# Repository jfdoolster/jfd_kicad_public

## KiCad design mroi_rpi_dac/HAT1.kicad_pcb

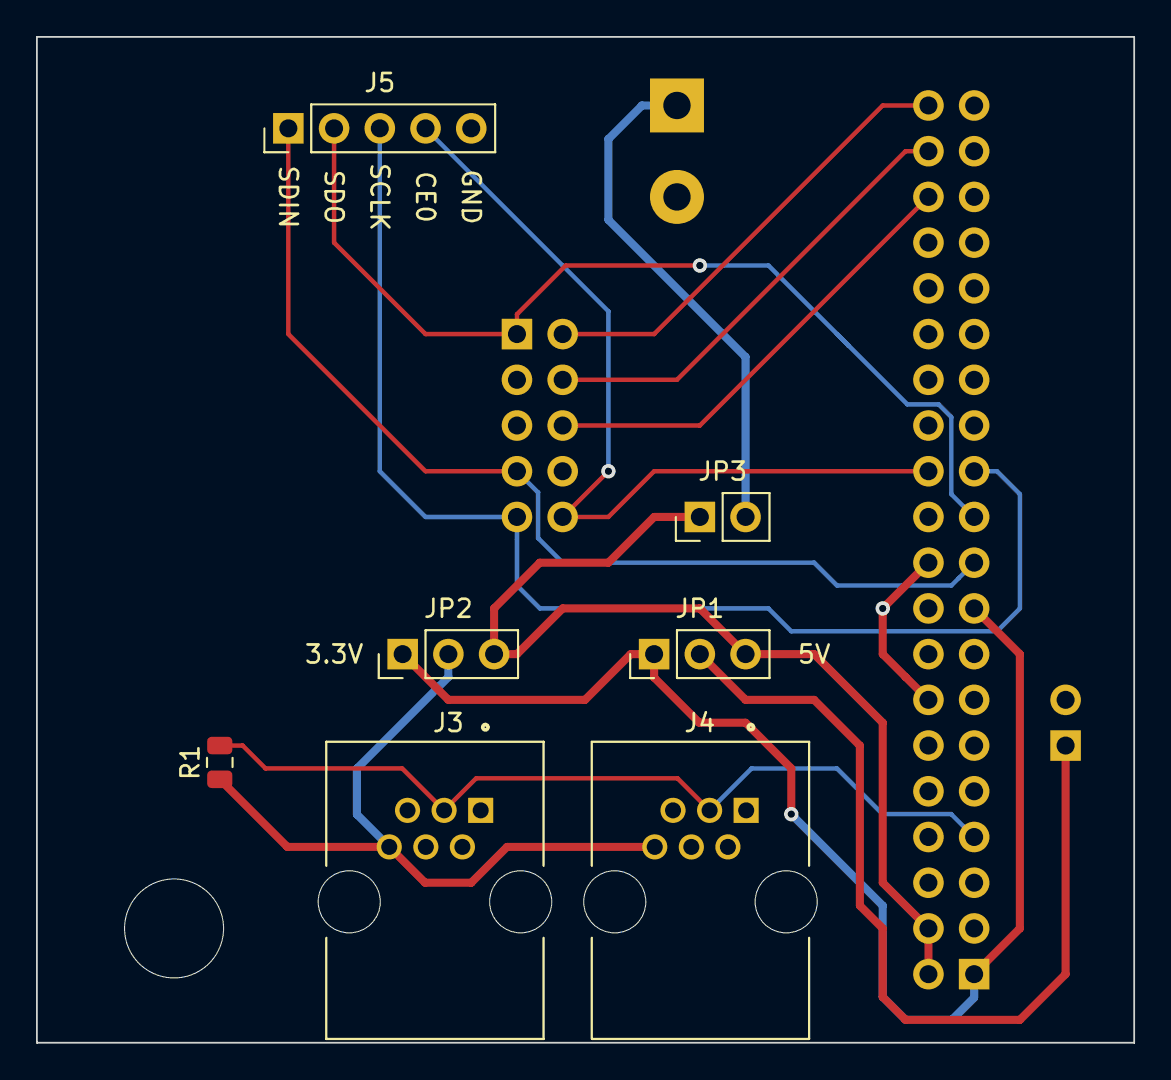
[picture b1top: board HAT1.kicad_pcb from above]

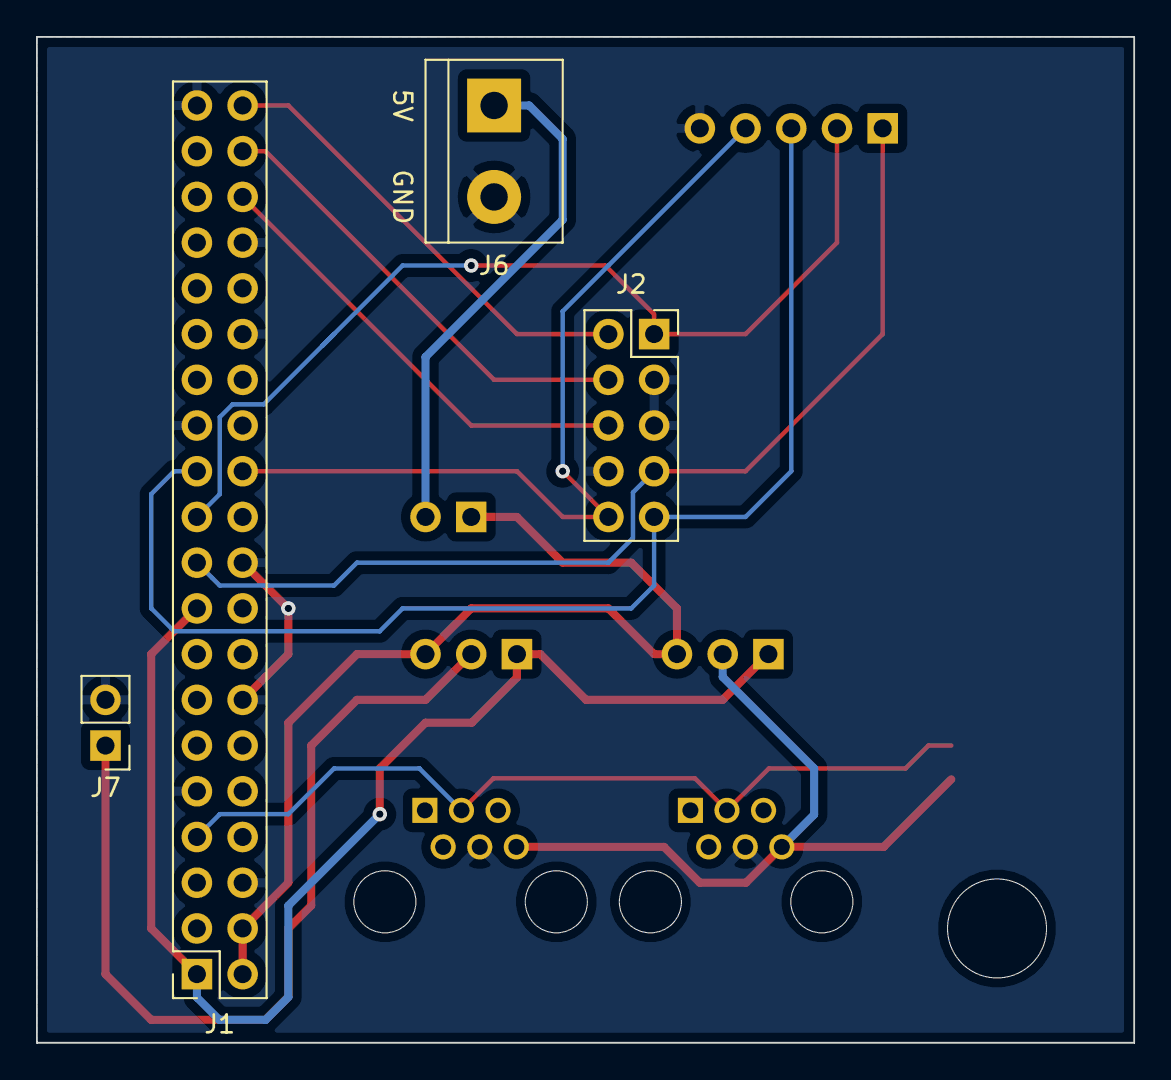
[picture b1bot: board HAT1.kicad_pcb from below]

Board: 2 copper layers, 61.0 x 55.9 mm, 11 parts (4 on the bottom side), 14 nets.

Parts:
J1: RaspberryPi; PinSocket_2x20_P2.54mm_Vertical
J2: AD5754; PinSocket_2x05_P2.54mm_Vertical
J3, J4: RJE0166001; AMPHENOL_RJE0166001
J5: Debug; PinHeader_1x05_P2.54mm_Vertical
J6: Power_Out; TerminalBlock_bornier-2_P5.08mm
J7: Fan; PinHeader_1x02_P2.54mm_Vertical
JP1: Power_Fan; PinHeader_1x03_P2.54mm_Vertical
JP2: Power_1Wire; PinHeader_1x03_P2.54mm_Vertical
JP3: Jumper_NC_Small; PinHeader_1x02_P2.54mm_Vertical
R1: 4.7k; R_0805_2012Metric

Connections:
1WIRE: J1.7, J3.3, J4.3, R1.2
2COMP: J1.40, J2.2
+3V3: J1.1, J1.17, JP1.1, JP2.1
+5V: J1.2, J1.4, JP1.3, JP2.3, JP3.1
CE0: J1.24, J2.10, J5.4
CLR: J1.38, J2.4
GNDREF: J1.6, J1.9, J1.14, J1.20, J1.25, J1.30, J1.34, J1.39, J2.3, J2.5, J2.8, J3.4, J4.4, J5.5, J6.2, J7.2
LDAC: J1.36, J2.6
unnamed: J3.6, J4.6, JP2.2, R1.1
unnamed: J6.1, JP3.2
unnamed: J7.1, JP1.2
SCLK: J1.23, J2.9, J5.3
SDIN: J1.19, J2.7, J5.1
SDO: J1.21, J2.1, J5.2

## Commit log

2024-01-16 -mMROI 1-wire T sensor RPi hat
2024-01-22 start pcb layout
